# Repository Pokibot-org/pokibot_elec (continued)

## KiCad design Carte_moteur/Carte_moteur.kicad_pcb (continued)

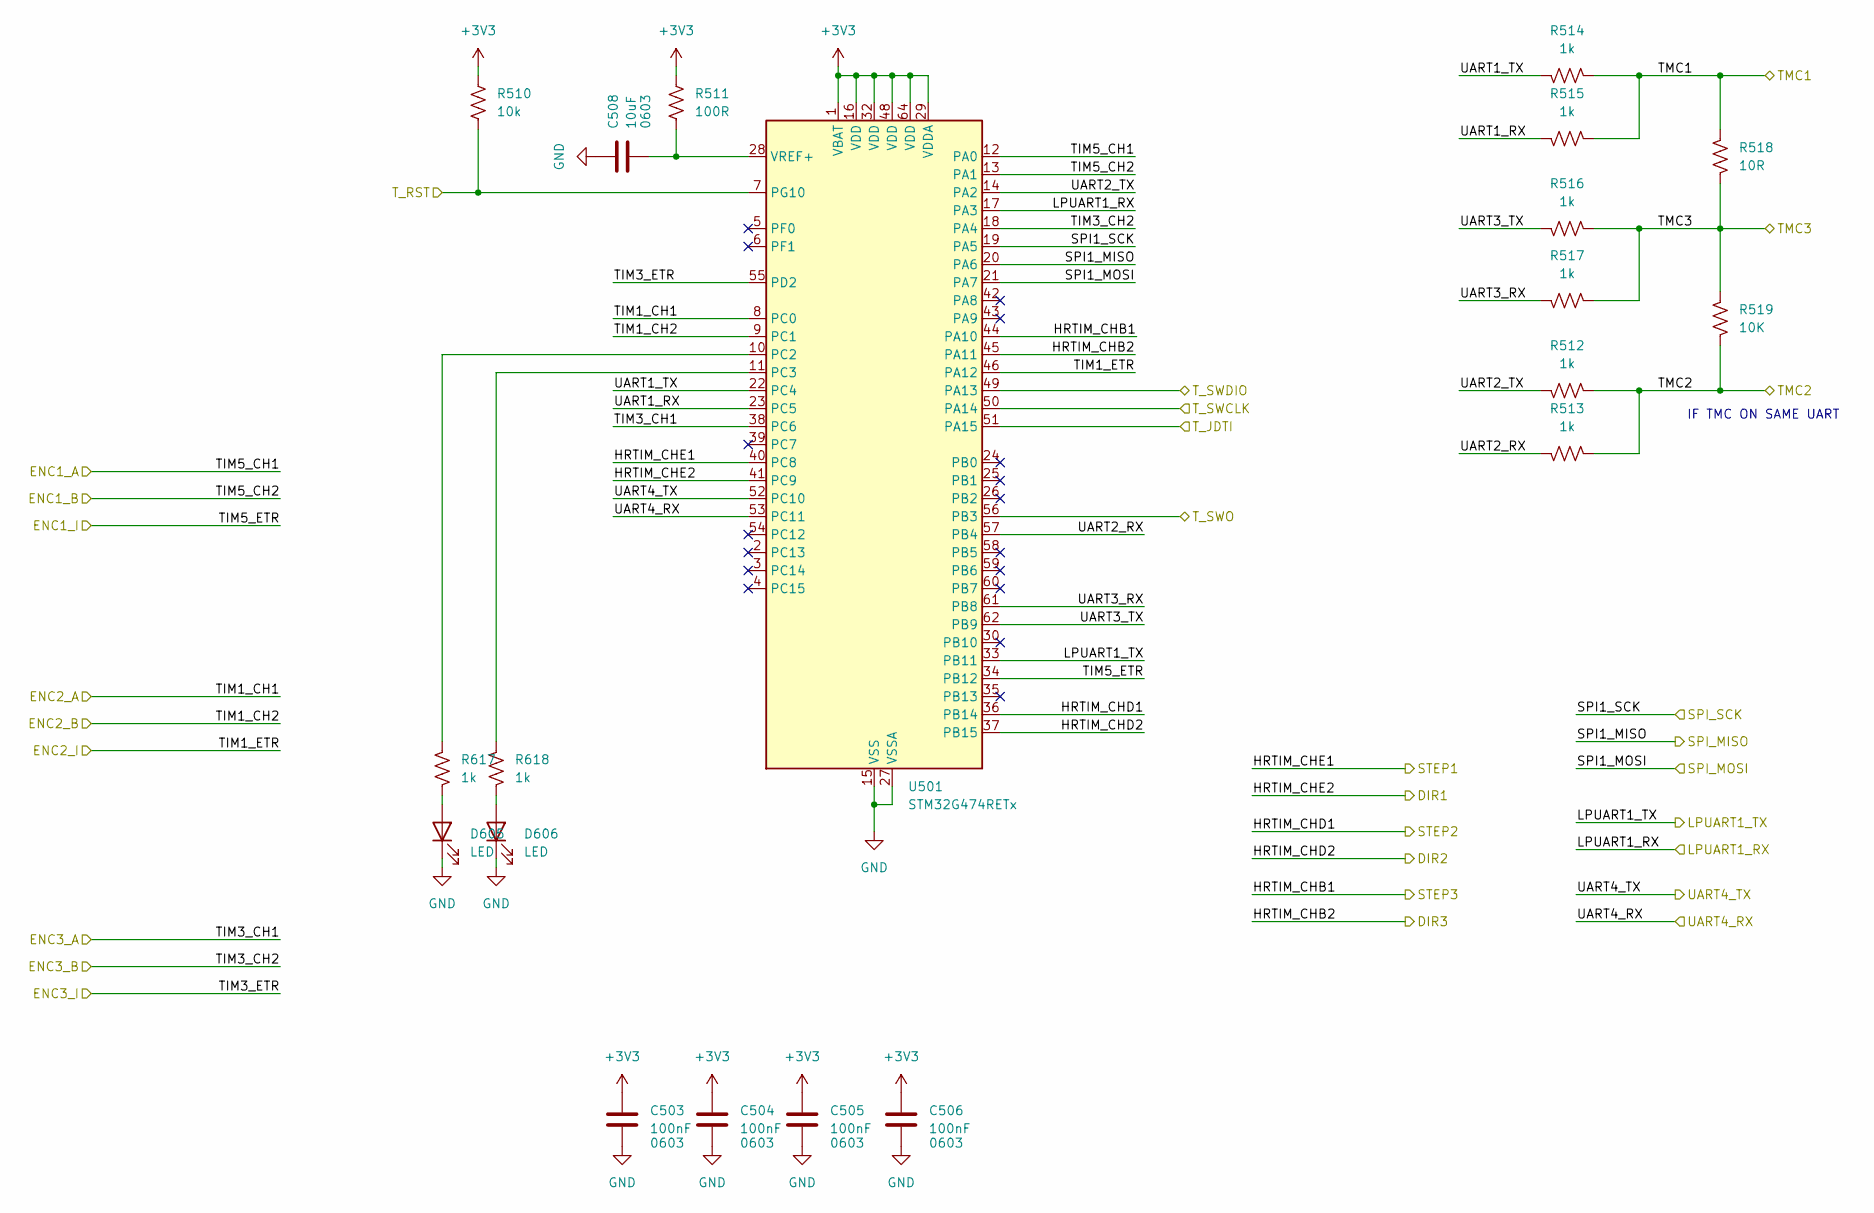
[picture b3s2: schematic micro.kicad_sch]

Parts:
C503, C504, C505, C506: 100nF; C_0603_1608Metric_Pad1.08x0.95mm_HandSolder
C508: 10uF; C_0603_1608Metric_Pad1.08x0.95mm_HandSolder
D605, D606: LED; LED_0805_2012Metric_Pad1.15x1.40mm_HandSolder
R510: 10k; R_0603_1608Metric_Pad0.98x0.95mm_HandSolder
R511: 100R; R_0603_1608Metric_Pad0.98x0.95mm_HandSolder
R512, R513, R514, R515, R516, R517, R617, R618: 1k; R_0603_1608Metric_Pad0.98x0.95mm_HandSolder
R518: 10R; R_0805_2012Metric_Pad1.20x1.40mm_HandSolder
R519: 10K; R_0805_2012Metric_Pad1.20x1.40mm_HandSolder
U501: STM32G474RETx; LQFP-64_10x10mm_P0.5mm

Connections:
+3V3: C503.1, C504.1, C505.1, C506.1, R510.2, R511.2, U501.1 (VBAT), U501.16 (VDD), U501.29 (VDDA), U501.32 (VDD), U501.48 (VDD), U501.64 (VDD); also elsewhere on the board
/micro/HRTIM_CHB1: U501.44 (PA10); also elsewhere on the board
/micro/HRTIM_CHB2: U501.45 (PA11); also elsewhere on the board
/micro/HRTIM_CHD1: U501.36 (PB14); also elsewhere on the board
/micro/HRTIM_CHD2: U501.37 (PB15); also elsewhere on the board
/micro/HRTIM_CHE1: U501.40 (PC8); also elsewhere on the board
/micro/HRTIM_CHE2: U501.41 (PC9); also elsewhere on the board
/micro/LPUART1_RX: U501.17 (PA3); also elsewhere on the board
/micro/LPUART1_TX: U501.33 (PB11); also elsewhere on the board
/micro/SPI1_MISO: U501.20 (PA6); also elsewhere on the board
/micro/SPI1_MOSI: U501.21 (PA7); also elsewhere on the board
/micro/SPI1_SCK: U501.19 (PA5); also elsewhere on the board
/micro/TIM1_CH1: U501.8 (PC0); also elsewhere on the board
/micro/TIM1_CH2: U501.9 (PC1); also elsewhere on the board
/micro/TIM1_ETR: U501.46 (PA12); also elsewhere on the board
/micro/TIM3_CH1: U501.38 (PC6); also elsewhere on the board
/micro/TIM3_CH2: U501.18 (PA4); also elsewhere on the board
/micro/TIM3_ETR: U501.55 (PD2); also elsewhere on the board
/micro/TIM5_CH1: U501.12 (PA0); also elsewhere on the board
/micro/TIM5_CH2: U501.13 (PA1); also elsewhere on the board
/micro/TIM5_ETR: U501.34 (PB12); also elsewhere on the board
/micro/TMC1: R514.1, R515.1, R518.1; also elsewhere on the board
/micro/TMC2: R512.1, R513.1, R519.2; also elsewhere on the board
/micro/TMC3: R516.1, R517.1, R518.2, R519.1; also elsewhere on the board
/micro/T_JDTI: U501.51 (PA15); also elsewhere on the board
/micro/T_RST: R510.1, U501.7 (PG10); also elsewhere on the board
/micro/T_SWCLK: U501.50 (PA14); also elsewhere on the board
/micro/T_SWDIO: U501.49 (PA13); also elsewhere on the board
/micro/T_SWO: U501.56 (PB3); also elsewhere on the board
/micro/UART1_RX: R515.2, U501.23 (PC5)
/micro/UART1_TX: R514.2, U501.22 (PC4)
/micro/UART2_RX: R513.2, U501.57 (PB4)
/micro/UART2_TX: R512.2, U501.14 (PA2)
/micro/UART3_RX: R517.2, U501.61 (PB8)
/micro/UART3_TX: R516.2, U501.62 (PB9)
/micro/UART4_RX: U501.53 (PC11); also elsewhere on the board
/micro/UART4_TX: U501.52 (PC10); also elsewhere on the board
GND: C503.2, C504.2, C505.2, C506.2, C508.1, D605.1 (K), D606.1 (K), U501.15 (VSS), U501.27 (VSSA), U501.31 (VSS), U501.47 (VSS), U501.63 (VSS); also elsewhere on the board
unnamed: D605.2 (A), R617.2
unnamed: D606.2 (A), R618.2
unnamed: R617.1, U501.10 (PC2)
unnamed: R618.1, U501.11 (PC3)
unnamed: C508.2, R511.1, U501.28 (VREF+)

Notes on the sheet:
IF TMC ON SAME UART

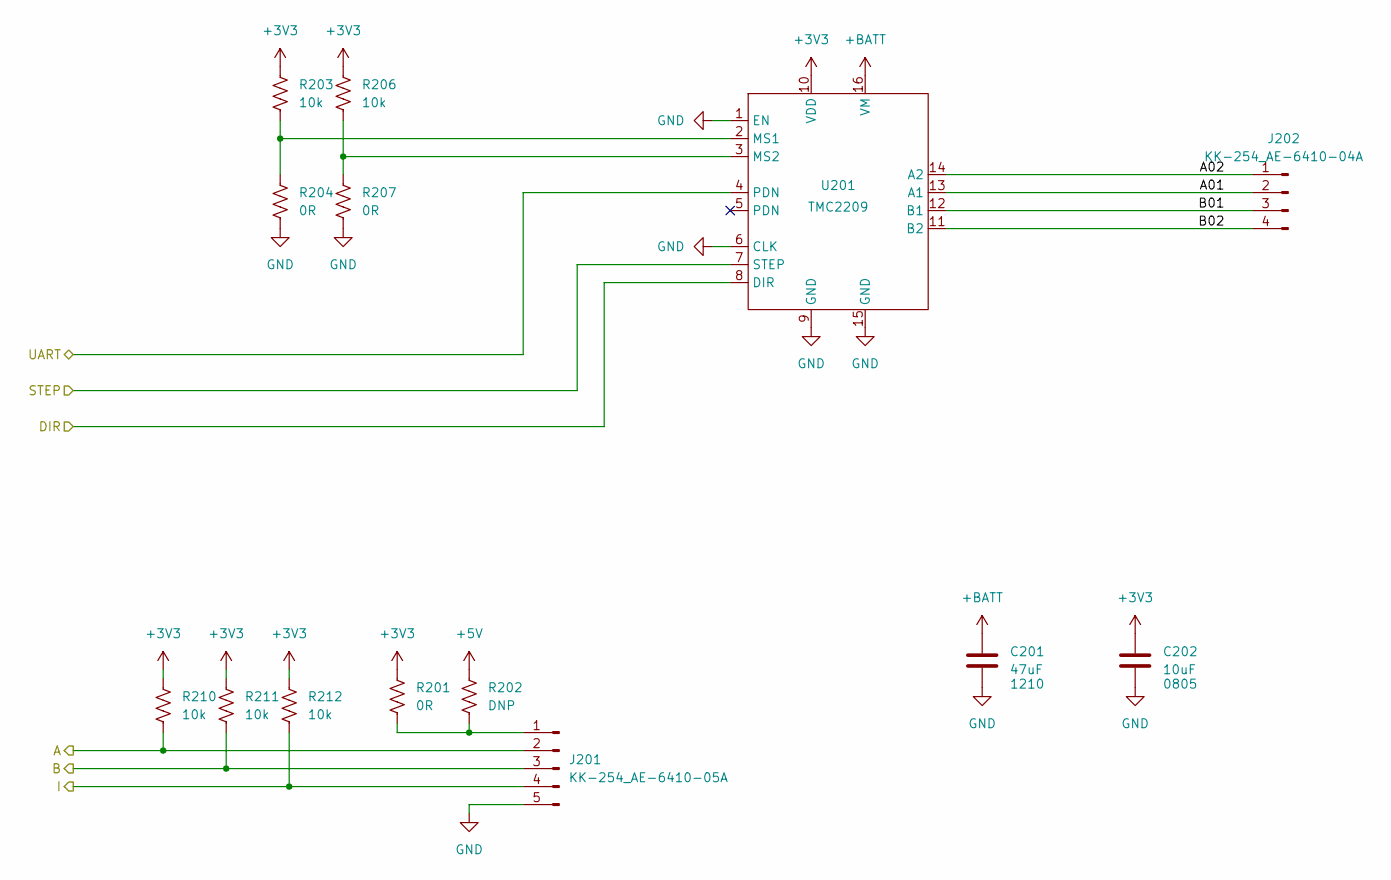
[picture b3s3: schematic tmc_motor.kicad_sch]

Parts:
C201: 47uF; C_1210_3225Metric_Pad1.33x2.70mm_HandSolder
C202: 10uF; C_0805_2012Metric_Pad1.18x1.45mm_HandSolder
J201: KK-254_AE-6410-05A; Molex_KK-254_AE-6410-05A_1x05_P2.54mm_Vertical
J202: KK-254_AE-6410-04A; Molex_KK-254_AE-6410-04A_1x04_P2.54mm_Vertical
R201, R204, R207: 0R; R_0603_1608Metric_Pad0.98x0.95mm_HandSolder
R202: DNP; R_0603_1608Metric_Pad0.98x0.95mm_HandSolder
R203, R206: 10k; R_0805_2012Metric_Pad1.20x1.40mm_HandSolder
R210, R211, R212: 10k; R_0603_1608Metric_Pad0.98x0.95mm_HandSolder
U201: TMC2209

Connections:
+3V3: C202.1, R201.2, R203.1, R206.1, R210.2, R211.2, R212.2, U201.10 (VDD); also elsewhere on the board
+5V: R202.2; also elsewhere on the board
+BATT: C201.1, U201.16 (VM); also elsewhere on the board
/micro/HRTIM_CHE1: U201.7 (STEP); also elsewhere on the board
/micro/HRTIM_CHE2: U201.8 (DIR); also elsewhere on the board
/micro/TIM5_CH1: J201.2, R210.1; also elsewhere on the board
/micro/TIM5_CH2: J201.3, R211.1; also elsewhere on the board
/micro/TIM5_ETR: J201.4, R212.1; also elsewhere on the board
/micro/TMC1: U201.4 (PDN); also elsewhere on the board
/tmc_motor/A01: J202.2, U201.13 (A1)
/tmc_motor/A02: J202.1, U201.14 (A2)
/tmc_motor/B01: J202.3, U201.12 (B1)
/tmc_motor/B02: J202.4, U201.11 (B2)
GND: C201.2, C202.2, J201.5, R204.2, R207.2, U201.1 (EN), U201.6 (CLK), U201.9 (GND), U201.15 (GND); also elsewhere on the board
unnamed: J201.1, R201.1, R202.1
unnamed: R203.2, R204.1, U201.2 (MS1)
unnamed: R206.2, R207.1, U201.3 (MS2)

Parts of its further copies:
C301, C401: 47uF; C_1210_3225Metric_Pad1.33x2.70mm_HandSolder
C302, C402: 10uF; C_0805_2012Metric_Pad1.18x1.45mm_HandSolder
J301, J401: KK-254_AE-6410-05A; Molex_KK-254_AE-6410-05A_1x05_P2.54mm_Vertical
J302, J402: KK-254_AE-6410-04A; Molex_KK-254_AE-6410-04A_1x04_P2.54mm_Vertical
R301, R304, R307, R401, R404, R407: 0R; R_0603_1608Metric_Pad0.98x0.95mm_HandSolder
R302, R402: DNP; R_0603_1608Metric_Pad0.98x0.95mm_HandSolder
R303, R306, R403, R406: 10k; R_0805_2012Metric_Pad1.20x1.40mm_HandSolder
R523, R524, R525, R526, R527, R528: 10k; R_0603_1608Metric_Pad0.98x0.95mm_HandSolder
U301, U401: TMC2209

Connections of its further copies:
+3V3: C302.1, C402.1, R301.2, R303.1, R306.1, R401.2, R403.1, R406.1, R523.2, R524.2, R525.2, R526.2, R527.2, R528.2, U301.10 (VDD), U401.10 (VDD); also elsewhere on the board
+5V: R302.2, R402.2; also elsewhere on the board
+BATT: C301.1, C401.1, U301.16 (VM), U401.16 (VM); also elsewhere on the board
/micro/HRTIM_CHB1: U401.7 (STEP); also elsewhere on the board
/micro/HRTIM_CHB2: U401.8 (DIR); also elsewhere on the board
/micro/HRTIM_CHD1: U301.7 (STEP); also elsewhere on the board
/micro/HRTIM_CHD2: U301.8 (DIR); also elsewhere on the board
/micro/TIM1_CH1: J301.2, R523.1; also elsewhere on the board
/micro/TIM1_CH2: J301.3, R524.1; also elsewhere on the board
/micro/TIM1_ETR: J301.4, R525.1; also elsewhere on the board
/micro/TIM3_CH1: J401.2, R526.1; also elsewhere on the board
/micro/TIM3_CH2: J401.3, R527.1; also elsewhere on the board
/micro/TIM3_ETR: J401.4, R528.1; also elsewhere on the board
/micro/TMC2: U301.4 (PDN); also elsewhere on the board
/micro/TMC3: U401.4 (PDN); also elsewhere on the board
/tmc_motor1/A01: J302.2, U301.13 (A1)
/tmc_motor1/A02: J302.1, U301.14 (A2)
/tmc_motor1/B01: J302.3, U301.12 (B1)
/tmc_motor1/B02: J302.4, U301.11 (B2)
/tmc_motor2/A01: J402.2, U401.13 (A1)
/tmc_motor2/A02: J402.1, U401.14 (A2)
/tmc_motor2/B01: J402.3, U401.12 (B1)
/tmc_motor2/B02: J402.4, U401.11 (B2)
GND: C301.2, C302.2, C401.2, C402.2, J301.5, J401.5, R304.2, R307.2, R404.2, R407.2, U301.1 (EN), U301.6 (CLK), U301.9 (GND), U301.15 (GND), U401.1 (EN), U401.6 (CLK), U401.9 (GND), U401.15 (GND); also elsewhere on the board
unnamed: J301.1, R301.1, R302.1
unnamed: J401.1, R401.1, R402.1
unnamed: R303.2, R304.1, U301.2 (MS1)
unnamed: R306.2, R307.1, U301.3 (MS2)
unnamed: R403.2, R404.1, U401.2 (MS1)
unnamed: R406.2, R407.1, U401.3 (MS2)

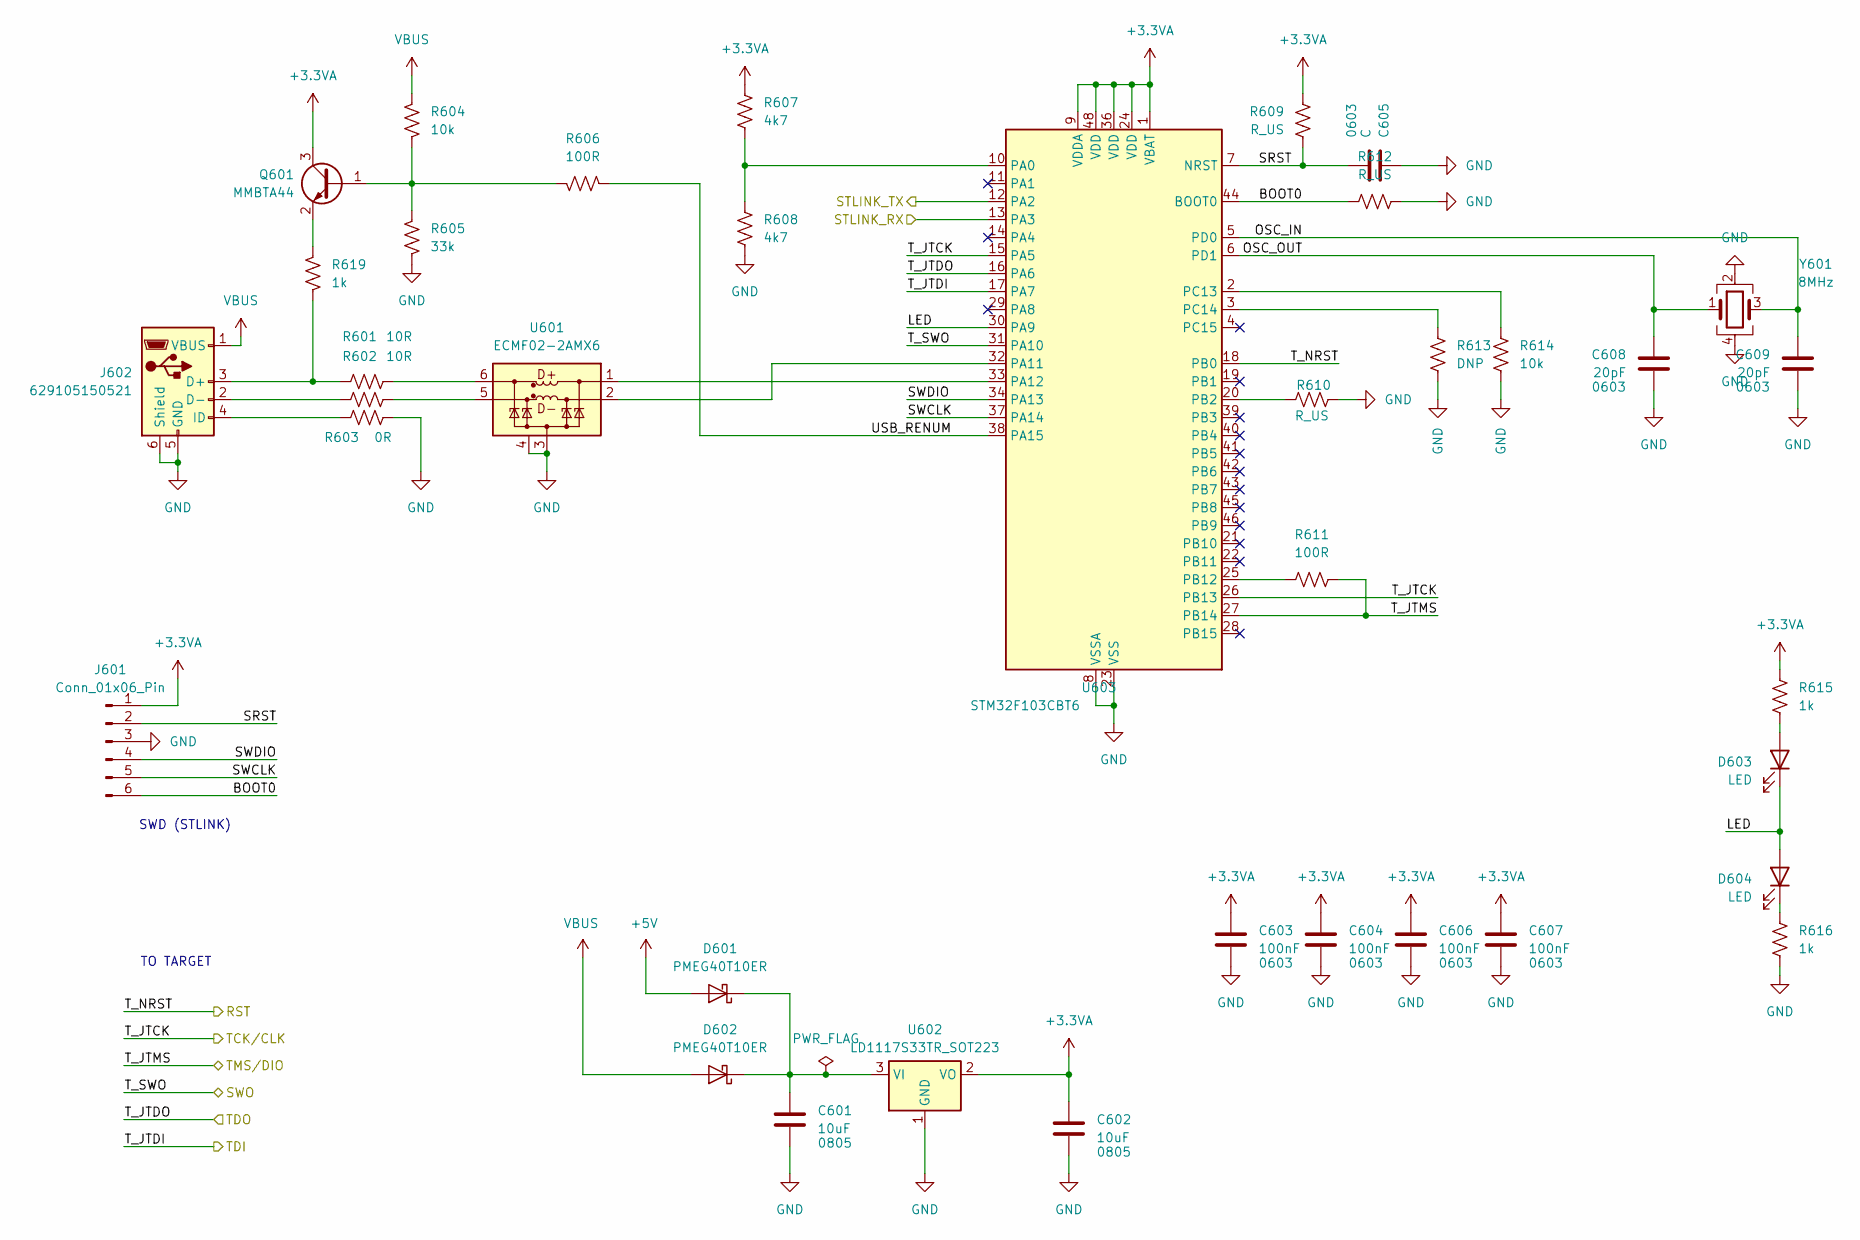
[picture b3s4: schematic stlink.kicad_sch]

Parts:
C601, C602: 10uF; C_0805_2012Metric_Pad1.18x1.45mm_HandSolder
C603, C604, C606, C607: 100nF; C_0603_1608Metric_Pad1.08x0.95mm_HandSolder
C605: C; C_0603_1608Metric_Pad1.08x0.95mm_HandSolder
C608, C609: 20pF; C_0603_1608Metric_Pad1.08x0.95mm_HandSolder
D601, D602: PMEG40T10ER; Nexperia_CFP3_SOD-123W
D603, D604: LED; LED_0805_2012Metric_Pad1.15x1.40mm_HandSolder
J601: Conn_01x06_Pin; PinHeader_1x06_P2.54mm_Vertical
J602: 629105150521; USB_Micro-B_Wuerth_629105150521
Q601: MMBTA44; SOT-23
R601, R602: 10R; R_0603_1608Metric_Pad0.98x0.95mm_HandSolder
R603: 0R; R_0603_1608Metric_Pad0.98x0.95mm_HandSolder
R604, R614: 10k; R_0603_1608Metric_Pad0.98x0.95mm_HandSolder
R605: 33k; R_0603_1608Metric_Pad0.98x0.95mm_HandSolder
R606, R611: 100R; R_0603_1608Metric_Pad0.98x0.95mm_HandSolder
R607, R608: 4k7; R_0603_1608Metric_Pad0.98x0.95mm_HandSolder
R609, R610, R612: R_US; R_0603_1608Metric_Pad0.98x0.95mm_HandSolder
R613: DNP; R_0603_1608Metric_Pad0.98x0.95mm_HandSolder
R615, R616, R619: 1k; R_0603_1608Metric_Pad0.98x0.95mm_HandSolder
U601: ECMF02-2AMX6; ST_UQFN-6L_1.5x1.7mm_P0.5mm
U602: LD1117S33TR_SOT223; SOT-223-3_TabPin2
U603: STM32F103CBT6; LQFP-48_7x7mm_P0.5mm
Y601: 8MHz; Crystal_SMD_EuroQuartz_MQ-4Pin_7.0x5.0mm_HandSoldering

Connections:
+3.3VA: C602.1, C603.1, C604.1, C606.1, C607.1, J601.1, Q601.3 (C), R607.1, R609.1, R615.1, U602.2 (VO), U603.1 (VBAT), U603.9 (VDDA), U603.24 (VDD), U603.36 (VDD), U603.48 (VDD)
+5V: D601.2 (A); also elsewhere on the board
/micro/UART4_RX: U603.12 (PA2); also elsewhere on the board
/micro/UART4_TX: U603.13 (PA3); also elsewhere on the board
/stlink/BOOT0: J601.6, R612.1, U603.44 (BOOT0)
/stlink/LED: D603.1 (K), D604.2 (A), U603.30 (PA9)
/stlink/OSC_IN: C609.1, U603.5 (PD0), Y601.3
/stlink/OSC_OUT: C608.1, U603.6 (PD1), Y601.1
/stlink/SRST: C605.2, J601.2, R609.2, U603.7 (NRST)
/stlink/SWCLK: J601.5, U603.37 (PA14)
/stlink/SWDIO: J601.4, U603.34 (PA13)
/stlink/T_JTCK: U603.15 (PA5), U603.26 (PB13); also elsewhere on the board
/stlink/T_JTDI: U603.17 (PA7); also elsewhere on the board
/stlink/T_JTDO: U603.16 (PA6)
/stlink/T_JTMS: R611.2, U603.27 (PB14); also elsewhere on the board
/stlink/T_NRST: U603.18 (PB0); also elsewhere on the board
/stlink/T_SWO: U603.31 (PA10); also elsewhere on the board
/stlink/USB_RENUM: R606.1, U603.38 (PA15)
GND: C601.2, C602.2, C603.2, C604.2, C605.1, C606.2, C607.2, C608.2, C609.2, J601.3, J602.5 (GND), J602.6 (Shield), R603.2, R605.2, R608.2, R610.2, R612.2, R613.2, R614.2, R616.2, U601.3 (GND), U601.4 (NC), U602.1 (GND), U603.8 (VSSA), U603.23 (VSS), U603.35 (VSS), U603.47 (VSS), Y601.2, Y601.4; also elsewhere on the board
unnamed: C601.1, D601.1 (K), D602.1 (K), U602.3 (VI)
unnamed: D603.2 (A), R615.2
unnamed: D604.1 (K), R616.1
unnamed: J602.3 (D+), R601.1, R619.2
unnamed: J602.2 (D-), R602.1
unnamed: J602.4 (ID), R603.1
unnamed: Q601.1 (B), R604.2, R605.1, R606.2
unnamed: Q601.2 (E), R619.1
unnamed: U601.1 (D+_in), U603.33 (PA12)
unnamed: R601.2, U601.6 (D+_out)
unnamed: U601.2 (D-_in), U603.32 (PA11)
unnamed: R602.2, U601.5 (D-_out)
unnamed: R607.2, R608.1, U603.10 (PA0)
unnamed: R610.1, U603.20 (PB2)
unnamed: R611.1, U603.25 (PB12)
unnamed: R614.1, U603.2 (PC13)
unnamed: R613.1, U603.3 (PC14)
VBUS: D602.2 (A), J602.1 (VBUS), R604.1

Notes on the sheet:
TO TARGET
SWD (STLINK)

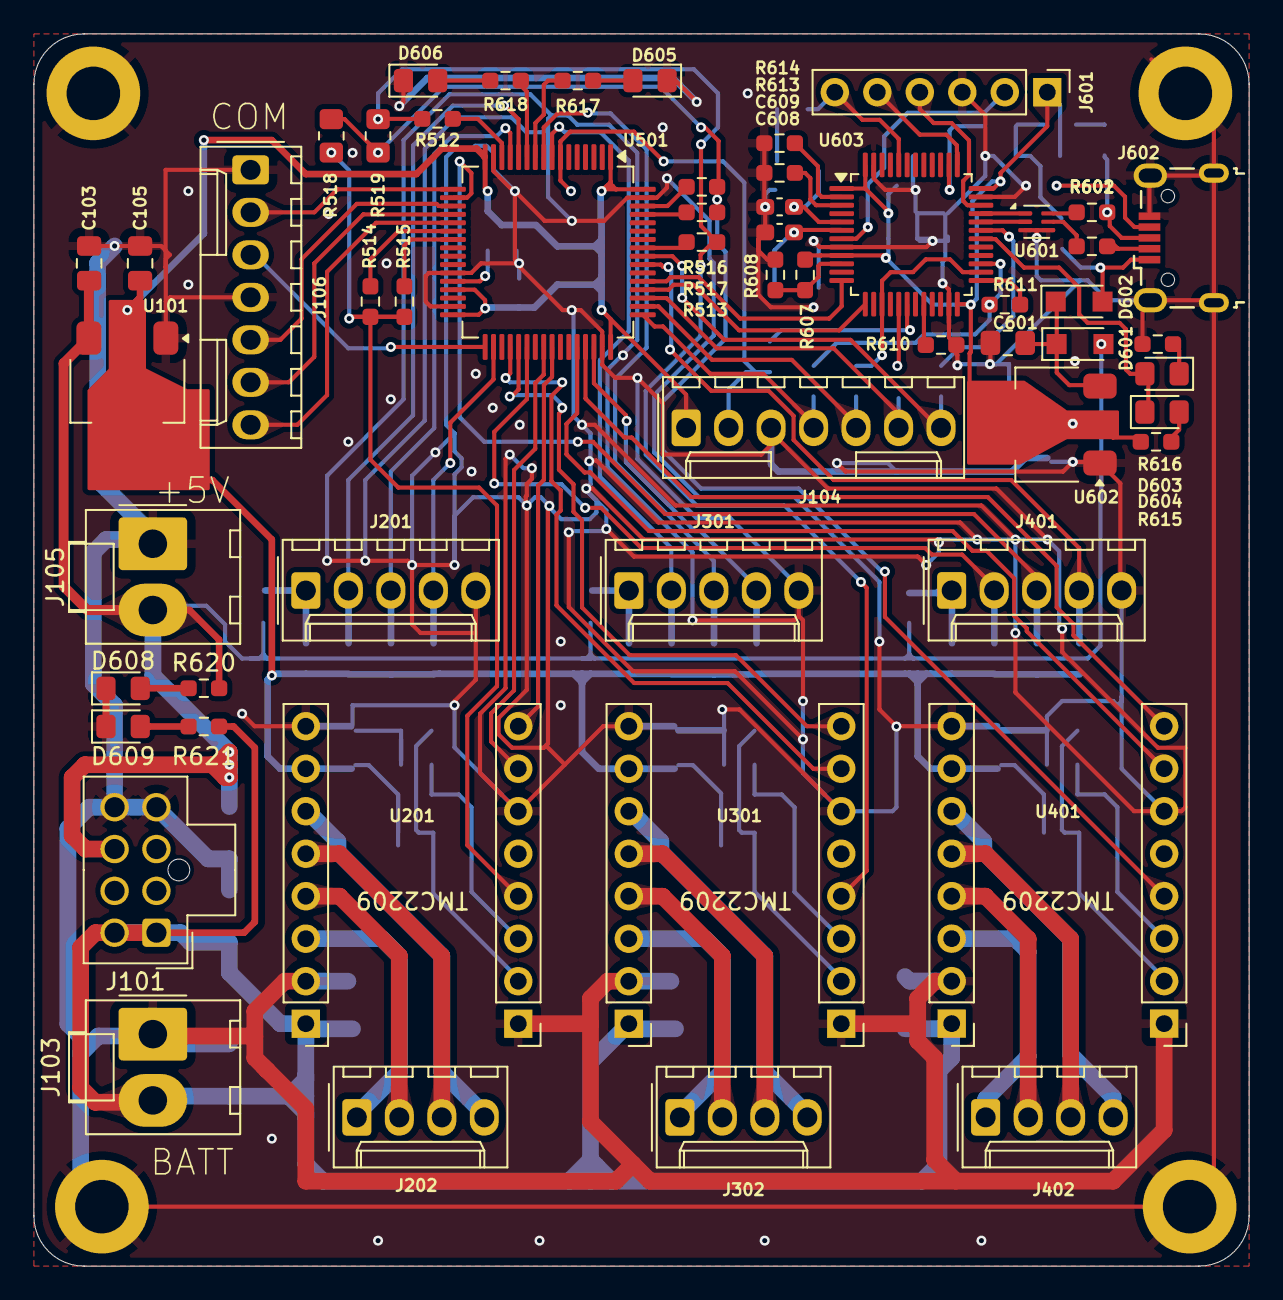
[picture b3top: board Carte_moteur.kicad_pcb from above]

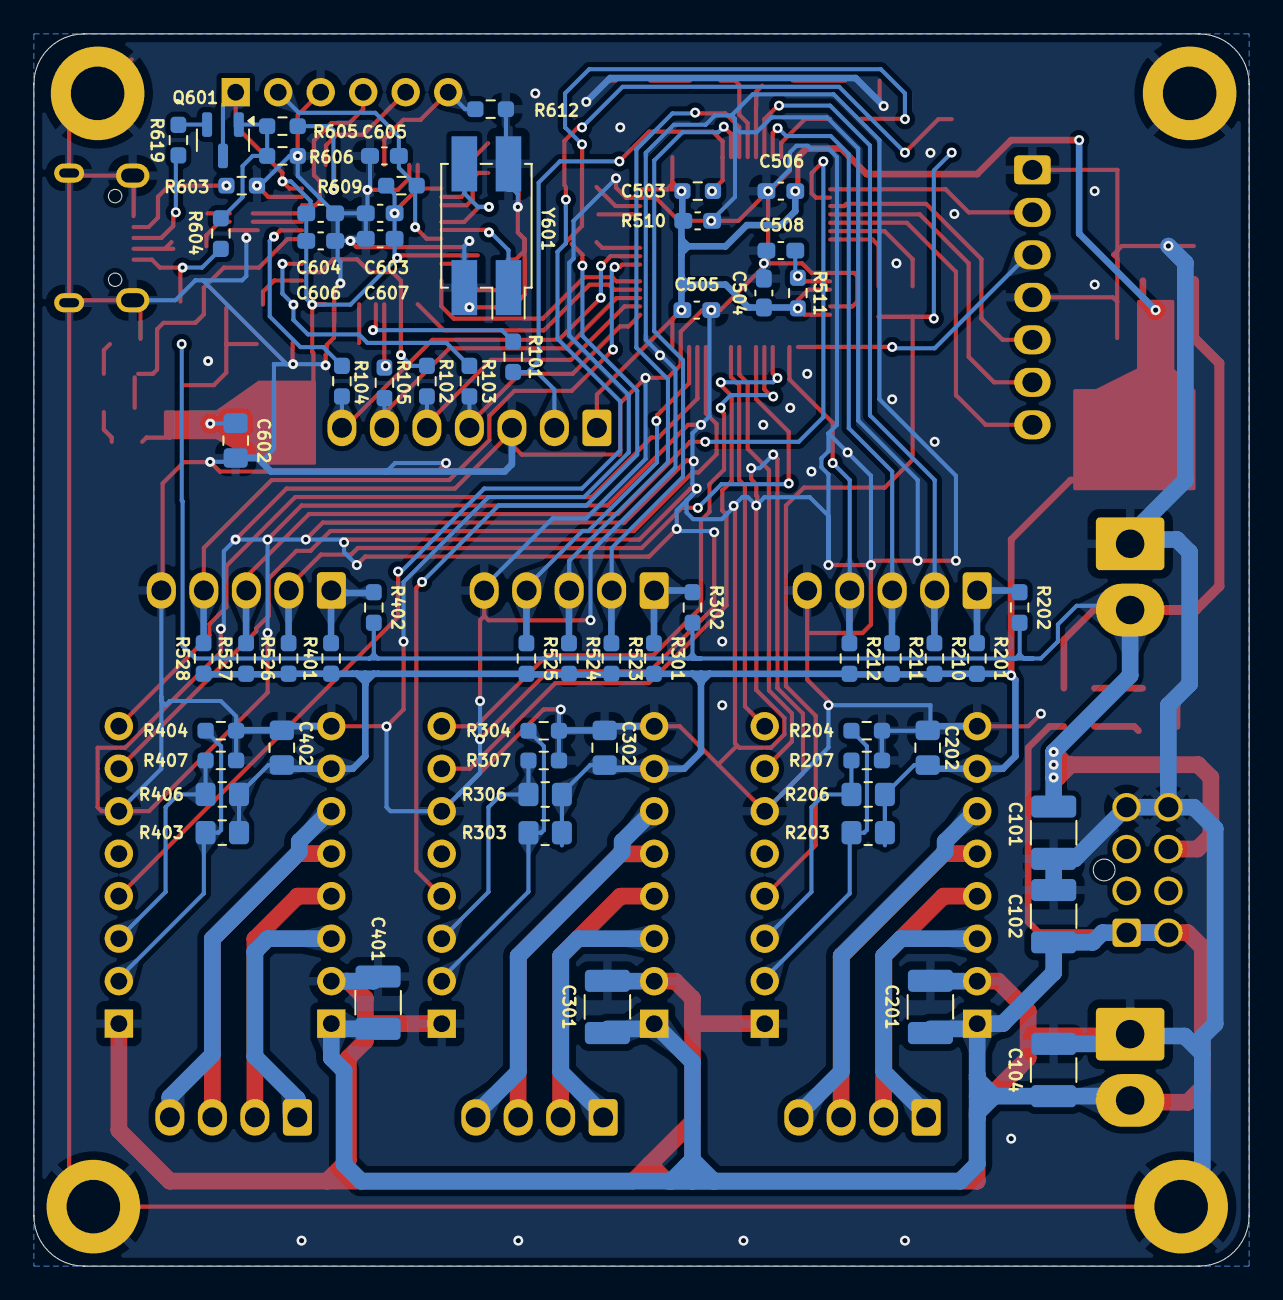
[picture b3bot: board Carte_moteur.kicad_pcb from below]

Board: 2 copper layers, 72.6 x 73.7 mm, 123 parts (63 on the bottom side), 100 nets.

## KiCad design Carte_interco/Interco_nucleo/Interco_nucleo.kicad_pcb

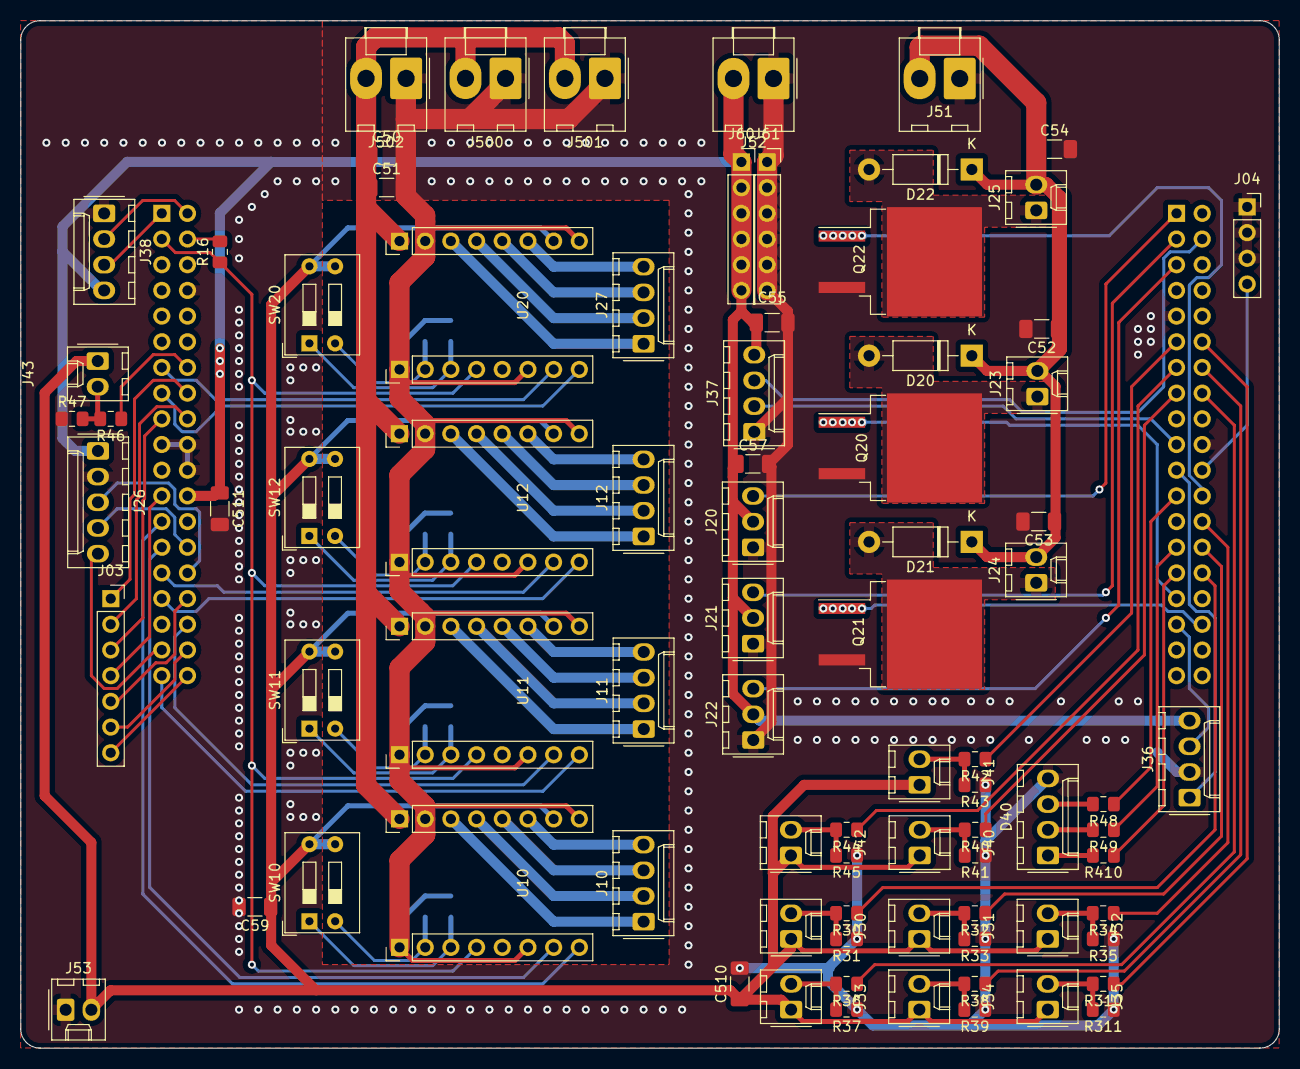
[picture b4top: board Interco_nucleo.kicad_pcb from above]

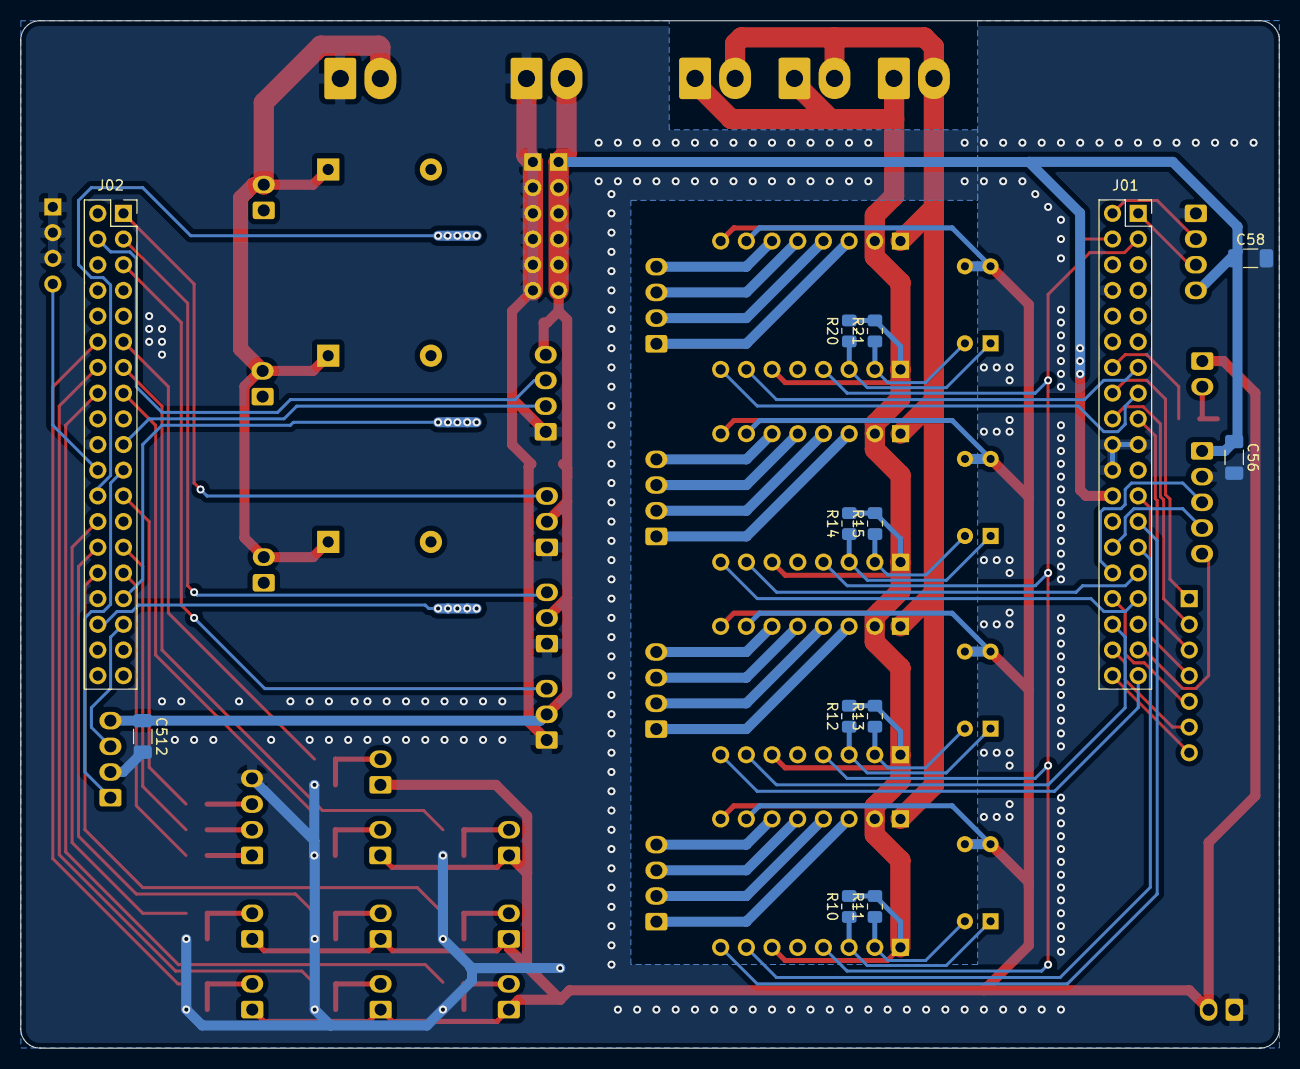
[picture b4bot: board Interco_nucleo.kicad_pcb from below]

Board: 2 copper layers, 124.5 x 101.6 mm, 96 parts (13 on the bottom side), 91 nets.

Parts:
C50, C51, C52, C53, C54, C55, C56, C57, C58, C59, C510, C511, C512: 100n; C_1206_3216Metric_Pad1.33x1.80mm_HandSolder
D20, D21, D22: 1N4007; D_DO-41_SOD81_P10.16mm_Horizontal
D40: LED_RGBK; Molex_KK-254_AE-6410-04A_1x04_P2.54mm_Vertical
J01, J02: Conn_02x19_Odd_Even; PinSocket_2x19_P2.54mm_Vertical
J03: unused_L; PinSocket_1x07_P2.54mm_Vertical
J04: unused_R; PinSocket_1x04_P2.54mm_Vertical
J10: MOT1; Molex_KK-254_AE-6410-04A_1x04_P2.54mm_Vertical
J11: MOT2; Molex_KK-254_AE-6410-04A_1x04_P2.54mm_Vertical
J12: MOT3; Molex_KK-254_AE-6410-04A_1x04_P2.54mm_Vertical
J20: servo orientation; Molex_KK-254_AE-6410-03A_1x03_P2.54mm_Vertical
J21: servo bras; Molex_KK-254_AE-6410-03A_1x03_P2.54mm_Vertical
J22: servo dicristaline; Molex_KK-254_AE-6410-03A_1x03_P2.54mm_Vertical
J23: pompe; Molex_KK-254_AE-6410-02A_1x02_P2.54mm_Vertical
J24: vanne; Molex_KK-254_AE-6410-02A_1x02_P2.54mm_Vertical
J25: electroaimant; Molex_KK-254_AE-6410-02A_1x02_P2.54mm_Vertical
J26: SNDBOARD; Molex_KK-254_AE-6410-05A_1x05_P2.54mm_Vertical
J27: MOT_actionneur; Molex_KK-254_AE-6410-04A_1x04_P2.54mm_Vertical
J30: SW01; Molex_KK-254_AE-6410-02A_1x02_P2.54mm_Vertical
J31: SW02; Molex_KK-254_AE-6410-02A_1x02_P2.54mm_Vertical
J32: SW03; Molex_KK-254_AE-6410-02A_1x02_P2.54mm_Vertical
J33: SW04; Molex_KK-254_AE-6410-02A_1x02_P2.54mm_Vertical
J34: SW05; Molex_KK-254_AE-6410-02A_1x02_P2.54mm_Vertical
J35: SW06; Molex_KK-254_AE-6410-02A_1x02_P2.54mm_Vertical
J36, J37: LORA; Molex_KK-254_AE-6410-04A_1x04_P2.54mm_Vertical
J38: 7SEG; Molex_KK-254_AE-6410-04A_1x04_P2.54mm_Vertical
J40: SWrobot; Molex_KK-254_AE-6410-02A_1x02_P2.54mm_Vertical
J41: SWcote; Molex_KK-254_AE-6410-02A_1x02_P2.54mm_Vertical
J42: Tirette; Molex_KK-254_AE-6410-02A_1x02_P2.54mm_Vertical
J43: reset; Molex_KK-254_AE-6410-02A_1x02_P2.54mm_Vertical
J51: 12V_IN; Molex_KK-396_A-41791-0002_1x02_P3.96mm_Vertical
J52: 5V_IN; Molex_KK-396_A-41791-0002_1x02_P3.96mm_Vertical
J53: 3V3_IN; Molex_KK-254_AE-6410-02A_1x02_P2.54mm_Vertical
J60: 5V_ext; PinSocket_1x06_P2.54mm_Vertical
J61: GND_ext; PinSocket_1x06_P2.54mm_Vertical
J500, J501, J502: VLIPO; Molex_KK-396_A-41791-0002_1x02_P3.96mm_Vertical
Q20, Q22: SW_pompe; TO-263-2
Q21: SW_vanne; TO-263-2
R10, R11, R12, R13, R14, R15, R16, R20, R21, R31, R33, R35, R37, R39, R41, R43, R45, R47, R311: 1k; C_0805_2012Metric_Pad1.18x1.45mm_HandSolder
R30, R32, R34, R36, R38, R40, R42, R44, R46, R310: 330; C_0805_2012Metric_Pad1.18x1.45mm_HandSolder
R48, R49, R410: 100; C_0805_2012Metric_Pad1.18x1.45mm_HandSolder
SW10, SW11, SW12, SW20: SW_DIP_x02; SW_DIP_SPSTx02_Slide_9.78x7.26mm_W7.62mm_P2.54mm
U10, U11, U12, U20: TMC2209

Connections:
/3V3: J01.16, J03.1
/5V: J01.18, J03.2
/5V_7SEG: C55.1, C56.1, C57.1, C58.1, C511.1, C512.1, J01.24, J20.2, J21.2, J22.2, J26.1, J36.4, J37.4, J38.4, J52.2, J60.1, J60.2, J60.3, J60.4, J60.5, J60.6
/7SEG_RX: J01.1, J38.3
/7SEG_TX: J01.2, J38.2
/A01: J10.2, U10.13 (A1)
/A02: J10.1, U10.14 (A2)
/A11: J11.2, U11.13 (A1)
/A12: J11.1, U11.14 (A2)
/A21: J12.2, U12.13 (A1)
/A22: J12.1, U12.14 (A2)
/A31: J27.2, U20.13 (A1)
/A32: J27.1, U20.14 (A2)
/B01: J10.3, U10.12 (B1)
/B02: J10.4, U10.11 (B2)
/B11: J11.3, U11.12 (B1)
/B12: J11.4, U11.11 (B2)
/B21: J12.3, U12.12 (B1)
/B22: J12.4, U12.11 (B2)
/B31: J27.3, U20.12 (B1)
/B32: J27.4, U20.11 (B2)
/D0: J01.25, U10.8 (DIR)
/D1: J01.37, U11.8 (DIR)
/D2: J01.31, U12.8 (DIR)
/D3: J01.15, U20.8 (DIR)
/LIDAR_RX: J02.21, J36.1
/LIDAR_TX: J02.33, J36.3
/LORA_RX: J02.4, J37.3
/LORA_TX: J02.19, J37.2
/PA_0: J01.28, J26.4
/PA_1: J01.30, J26.3
/PA_4: J01.32, J03.5
/PA_5: J02.11, R42.1
/PA_6: J02.13, R44.1
/PA_7: J02.15, R40.1
/PA_8: J02.23, R48.1
/PA_11: J02.14, R38.1
/PA_12: J02.12, R310.1
/PA_13: J01.13, U20.7 (STEP)
/PA_15: J01.17, J03.3
/PB_0: J01.34, U11.7 (STEP)
/PB_1: J02.24, Q22.1 (G)
/PB_2: J02.22, J04.4
/PB_3: J02.31, Q20.1 (G)
/PB_4: J02.27, R49.1
/PB_5: J02.29, R410.1
/PB_8: J02.3, J21.3
/PB_9: J02.5, J22.3
/PB_12: J02.16, R36.1
/PB_13: J02.30, R30.1
/PB_14: J02.28, R32.1
/PB_15: J02.26, R34.1
/PC_0: J01.38, J03.7
/PC_1: J01.36, J03.6
/PC_2: J01.35, J26.5
/PC_4: J02.34, Q21.1 (G)
/PC_9: J02.1, J20.3
/PC_12: J01.3, R16.1, U10.4 (PDN), U11.4 (PDN), U12.4 (PDN), U20.4 (PDN)
/PC_13: J01.23, J03.4
/PC_15: J01.27, U10.7 (STEP)
/PD_2: J01.4, R16.2
/PH_0: J01.29, U12.7 (STEP)
/RESET: J01.14, R46.1
/SW_3V3: C59.1, C510.1, J30.1, J31.1, J32.1, J33.1, J34.1, J35.1, J40.1, J41.1, J42.1, J43.1, J53.2, SW10.3, SW10.4, SW11.3, SW11.4, SW12.3, SW12.4, SW20.3, SW20.4, U10.10 (VDD), U11.10 (VDD), U12.10 (VDD), U20.10 (VDD)
/V_LIPO: C50.1, C51.1, J500.2, J501.2, J502.2, U10.16 (VM), U11.16 (VM), U12.16 (VM), U20.16 (VM)
/electroaimant_12V: C52.1, C53.1, C54.1, D20.1 (K), D21.1 (K), D22.1 (K), J23.2, J24.2, J25.2, J51.2
GND: C50.2, C51.2, C52.2, C53.2, C54.2, C55.2, C56.2, C57.2, C58.2, C59.2, C510.2, C511.2, C512.2, D40.4 (K), J01.8, J01.19, J01.20, J01.22, J02.9, J02.20, J02.32, J04.1, J04.2, J04.3, J20.1, J21.1, J22.1, J26.2, J36.2, J37.1, J38.1, J51.1, J52.1, J53.1, J61.1, J61.2, J61.3, J61.4, J61.5, J61.6, J500.1, J501.1, J502.1, Q20.3 (S), Q21.3 (S), Q22.3 (S), R10.2, R11.2, R12.2, R13.2, R14.2, R15.2, R20.2, R21.2, R31.1, R33.1, R35.1, R37.1, R39.1, R41.1, R43.1, R45.1, R47.1, R311.1, U10.1 (EN), U10.6 (CLK), U10.9 (GND), U10.15 (GND), U11.1 (EN), U11.6 (CLK), U11.9 (GND), U11.15 (GND), U12.1 (EN), U12.6 (CLK), U12.9 (GND), U12.15 (GND), U20.1 (EN), U20.6 (CLK), U20.9 (GND), U20.15 (GND)
unnamed: D20.2 (A), J23.1, Q20.2 (D)
unnamed: D21.2 (A), J24.1, Q21.2 (D)
unnamed: D22.2 (A), J25.1, Q22.2 (D)
unnamed: D40.1 (RA), R410.2
unnamed: D40.2 (GA), R49.2
unnamed: D40.3 (BA), R48.2
unnamed: J30.2, R30.2, R31.2
unnamed: J31.2, R32.2, R33.2
unnamed: J32.2, R34.2, R35.2
unnamed: J33.2, R36.2, R37.2
unnamed: J34.2, R38.2, R39.2
unnamed: J35.2, R310.2, R311.2
unnamed: J40.2, R40.2, R41.2
unnamed: J41.2, R42.2, R43.2
unnamed: J42.2, R44.2, R45.2
unnamed: J43.2, R46.2, R47.2
unnamed: R10.1, SW10.1, U10.3 (MS2)
unnamed: R11.1, SW10.2, U10.2 (MS1)
unnamed: R12.1, SW11.1, U11.3 (MS2)
unnamed: R13.1, SW11.2, U11.2 (MS1)
unnamed: R14.1, SW12.1, U12.3 (MS2)
unnamed: R15.1, SW12.2, U12.2 (MS1)
unnamed: R20.1, SW20.1, U20.3 (MS2)
unnamed: R21.1, SW20.2, U20.2 (MS1)
